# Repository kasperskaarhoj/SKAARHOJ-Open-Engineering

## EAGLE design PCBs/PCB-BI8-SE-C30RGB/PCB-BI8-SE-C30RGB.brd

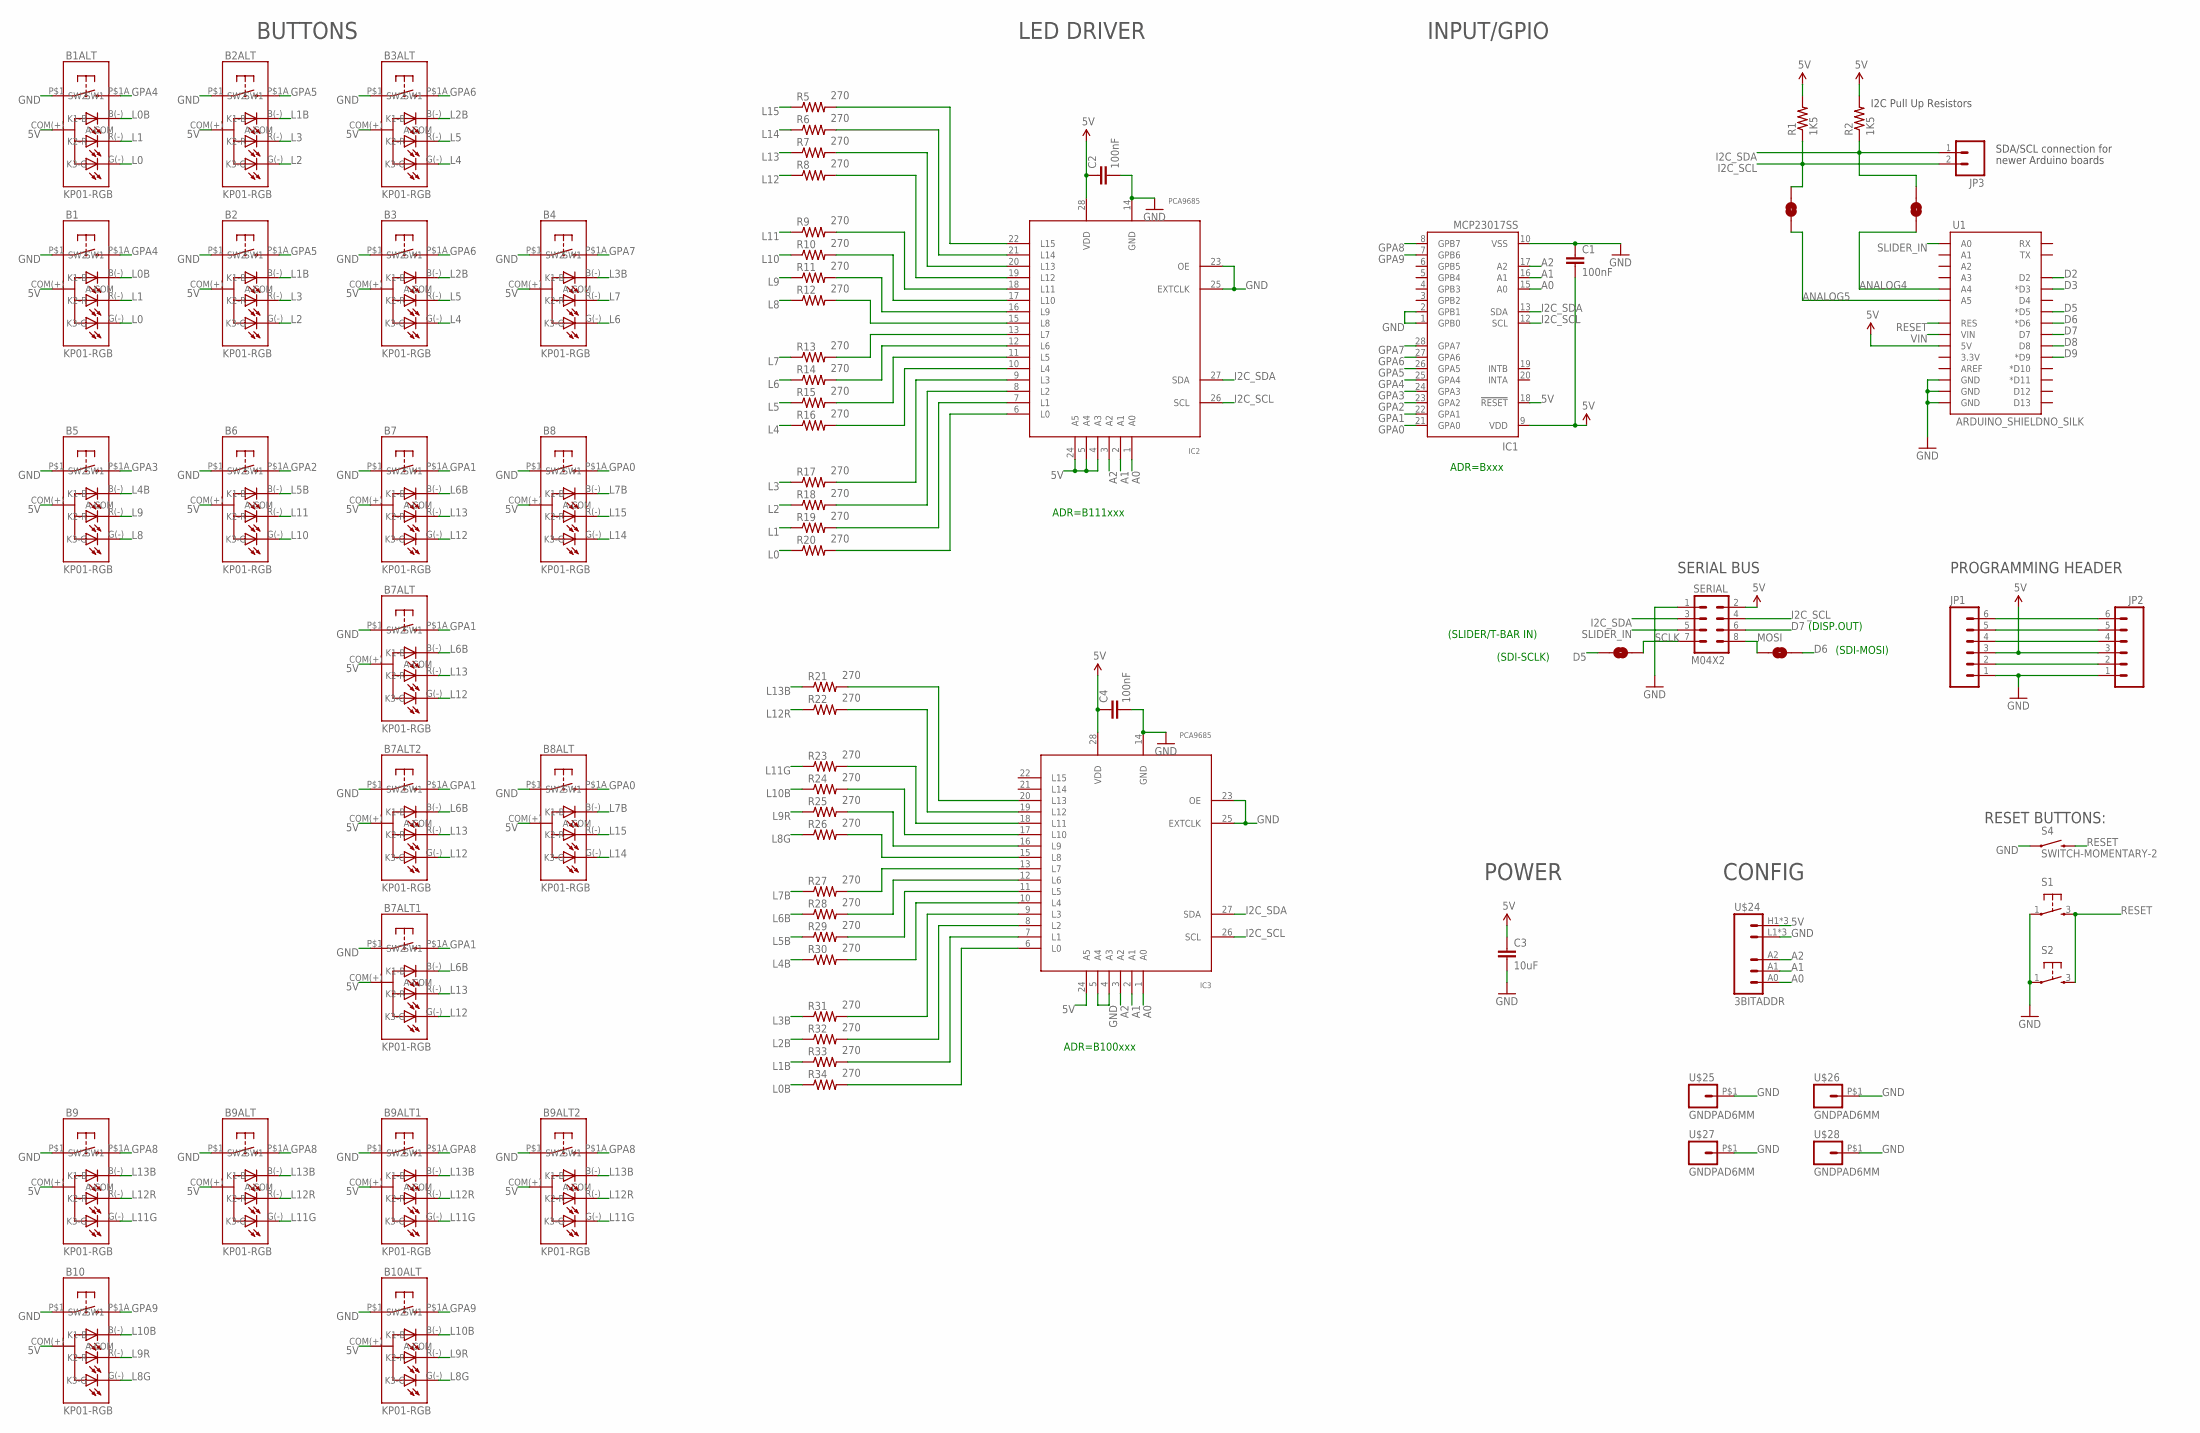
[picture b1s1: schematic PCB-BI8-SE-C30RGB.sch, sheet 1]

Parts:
B1, B1ALT, B2, B2ALT, B3, B3ALT, B4, B5, B7, B8, B9, B10: KP01-RGB; NKK-KP01
B6, B7ALT, B7ALT1, B7ALT2, B8ALT, B9ALT, B9ALT1, B9ALT2, B10ALT: KP01-RGB; NKK-KP01_LESSHOLES
C1, C2, C4: 100nF; 0603-CAP
C3: 10uF; 0805
IC1: MCP23017SS; SSOP28; MPN MCP23017-E/SS
IC2, IC3: PCA9685; TSSOP28
JP1, JP2: M06POLAR; MOLEX-1X6
JP3: M02PTH; 1X02
MOSI->D6: SOLDERJUMPERNC; SJ_2S
R1, R2: 1K5; 0603-RES
R5, R6, R7, R8, R9, R10, R11, R12, R13, R14, R15, R16, R17, R18, R19, R20, R21, R22, R23, R24, R25, R26, R27, R28, R29, R30, R31, R32, R33, R34: 270; 0603-RES
S1, S2: TAC_SWITCH; PUSHBUTTON
S3->A2, S3->A3: SOLDERJUMPERNC; SJ_2S
S4: SWITCH-MOMENTARY-2; TACTILE_SWITCH_TALL
SCLK->D5: SOLDERJUMPERNC; SJ_2S
SERIAL: M04X2; 2X4
U1: ARDUINO_SHIELDNO_SILK; DUEMILANOVE_VIAS
U$24: 3BITADDR
U$25, U$26, U$27, U$28: GNDPAD6MM; 3.2MMPAD6MM

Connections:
5V: B1.COM(+) (A-COM), B1ALT.COM(+) (A-COM), B2.COM(+) (A-COM), B2ALT.COM(+) (A-COM), B3.COM(+) (A-COM), B3ALT.COM(+) (A-COM), B4.COM(+) (A-COM), B5.COM(+) (A-COM), B6.COM(+) (A-COM), B7.COM(+) (A-COM), B7ALT.COM(+) (A-COM), B7ALT1.COM(+) (A-COM), B7ALT2.COM(+) (A-COM), B8.COM(+) (A-COM), B8ALT.COM(+) (A-COM), B9.COM(+) (A-COM), B9ALT.COM(+) (A-COM), B9ALT1.COM(+) (A-COM), B9ALT2.COM(+) (A-COM), B10.COM(+) (A-COM), B10ALT.COM(+) (A-COM), C1.2, C2.1, C3.1, C4.1, IC1.9 (VDD), IC1.18 (!RESET), IC2.4 (A3), IC2.5 (A4), IC2.24 (A5), IC2.28 (VDD), IC3.24 (A5), IC3.28 (VDD), JP1.3, JP2.3, R1.2, R2.2, SERIAL.2, U1.5V, U$24.H1 (VCC), U$24.H2 (VCC), U$24.H3 (VCC)
A0: IC1.15 (A0), IC2.1 (A0), IC3.1 (A0), U$24.A0
A1: IC1.16 (A1), IC2.2 (A1), IC3.2 (A1), U$24.A1
A2: IC1.17 (A2), IC2.3 (A2), IC3.3 (A2), U$24.A2
ANALOG4: S3->A3.2, U1.A4
ANALOG5: S3->A2.2, U1.A5
D2: U1.D2
D3: U1.D3 (*D3)
D5: SCLK->D5.1, U1.D5 (*D5)
D6: MOSI->D6.2, U1.D6 (*D6)
D7: SERIAL.6, U1.D7
D8: U1.D8
D9: U1.D9 (*D9)
GND: B1.P$1 (SW1), B1ALT.P$1 (SW1), B2.P$1 (SW1), B2ALT.P$1 (SW1), B3.P$1 (SW1), B3ALT.P$1 (SW1), B4.P$1 (SW1), B5.P$1 (SW1), B6.P$1 (SW1), B7.P$1 (SW1), B7ALT.P$1 (SW1), B7ALT1.P$1 (SW1), B7ALT2.P$1 (SW1), B8.P$1 (SW1), B8ALT.P$1 (SW1), B9.P$1 (SW1), B9ALT.P$1 (SW1), B9ALT1.P$1 (SW1), B9ALT2.P$1 (SW1), B10.P$1 (SW1), B10ALT.P$1 (SW1), C1.1, C2.2, C3.2, C4.2, IC1.1 (GPB0), IC1.2 (GPB1), IC1.10 (VSS), IC2.14 (GND), IC2.23 (OE), IC2.25 (EXTCLK), IC3.4 (A3), IC3.5 (A4), IC3.14 (GND), IC3.23 (OE), IC3.25 (EXTCLK), JP1.1, JP2.1, S1.1, S2.1, S4.A2 (1), SERIAL.1, U1.GND@0 (GND), U1.GND@1 (GND), U1.GND@2 (GND), U$24.L1 (GND), U$24.L2 (GND), U$24.L3 (GND), U$25.P$1, U$26.P$1, U$27.P$1, U$28.P$1
GPA0: B8.P$1A (SW2), B8ALT.P$1A (SW2), IC1.21 (GPA0)
GPA1: B7.P$1A (SW2), B7ALT.P$1A (SW2), B7ALT1.P$1A (SW2), B7ALT2.P$1A (SW2), IC1.22 (GPA1)
GPA2: B6.P$1A (SW2), IC1.23 (GPA2)
GPA3: B5.P$1A (SW2), IC1.24 (GPA3)
GPA4: B1.P$1A (SW2), B1ALT.P$1A (SW2), IC1.25 (GPA4)
GPA5: B2.P$1A (SW2), B2ALT.P$1A (SW2), IC1.26 (GPA5)
GPA6: B3.P$1A (SW2), B3ALT.P$1A (SW2), IC1.27 (GPA6)
GPA7: B4.P$1A (SW2), IC1.28 (GPA7)
GPA8: B9.P$1A (SW2), B9ALT.P$1A (SW2), B9ALT1.P$1A (SW2), B9ALT2.P$1A (SW2), IC1.8 (GPB7)
GPA9: B10.P$1A (SW2), B10ALT.P$1A (SW2), IC1.7 (GPB6)
I2C_SCL: IC1.12 (SCL), IC2.26 (SCL), IC3.26 (SCL), JP3.2, R1.1, S3->A2.1, SERIAL.4
I2C_SDA: IC1.13 (SDA), IC2.27 (SDA), IC3.27 (SDA), JP3.1, R2.1, S3->A3.1, SERIAL.3
L0: B1.G(-) (K3-G), B1ALT.G(-) (K3-G), R20.1
L0B: B1.B(-) (K1-B), B1ALT.B(-) (K1-B), R34.1
L1: B1.R(-) (K2-R), B1ALT.R(-) (K2-R), R19.1
L1B: B2.B(-) (K1-B), B2ALT.B(-) (K1-B), R33.1
L2: B2.G(-) (K3-G), B2ALT.G(-) (K3-G), R18.1
L2B: B3.B(-) (K1-B), B3ALT.B(-) (K1-B), R32.1
L3: B2.R(-) (K2-R), B2ALT.R(-) (K2-R), R17.1
L3B: B4.B(-) (K1-B), R31.1
L4: B3.G(-) (K3-G), B3ALT.G(-) (K3-G), R16.1
L4B: B5.B(-) (K1-B), R30.1
L5: B3.R(-) (K2-R), B3ALT.R(-) (K2-R), R15.1
L5B: B6.B(-) (K1-B), R29.1
L6: B4.G(-) (K3-G), R14.1
L6B: B7.B(-) (K1-B), B7ALT.B(-) (K1-B), B7ALT1.B(-) (K1-B), B7ALT2.B(-) (K1-B), R28.1
L7: B4.R(-) (K2-R), R13.1
L7B: B8.B(-) (K1-B), B8ALT.B(-) (K1-B), R27.1
L8: B5.G(-) (K3-G), R12.1
L8G: B10.G(-) (K3-G), B10ALT.G(-) (K3-G), R26.1
L9: B5.R(-) (K2-R), R11.1
L9R: B10.R(-) (K2-R), B10ALT.R(-) (K2-R), R25.1
L10: B6.G(-) (K3-G), R10.1
L10B: B10.B(-) (K1-B), B10ALT.B(-) (K1-B), R24.1
L11: B6.R(-) (K2-R), R9.1
L11G: B9.G(-) (K3-G), B9ALT.G(-) (K3-G), B9ALT1.G(-) (K3-G), B9ALT2.G(-) (K3-G), R23.1
L12: B7.G(-) (K3-G), B7ALT.G(-) (K3-G), B7ALT1.G(-) (K3-G), B7ALT2.G(-) (K3-G), R8.1
L12R: B9.R(-) (K2-R), B9ALT.R(-) (K2-R), B9ALT1.R(-) (K2-R), B9ALT2.R(-) (K2-R), R22.1
L13: B7.R(-) (K2-R), B7ALT.R(-) (K2-R), B7ALT1.R(-) (K2-R), B7ALT2.R(-) (K2-R), R7.1
L13B: B9.B(-) (K1-B), B9ALT.B(-) (K1-B), B9ALT1.B(-) (K1-B), B9ALT2.B(-) (K1-B), R21.1
L14: B8.G(-) (K3-G), B8ALT.G(-) (K3-G), R6.1
L15: B8.R(-) (K2-R), B8ALT.R(-) (K2-R), R5.1
MOSI: MOSI->D6.1, SERIAL.8
unnamed: JP1.2, JP2.2
unnamed: IC3.13 (L7), R27.2
unnamed: IC3.12 (L6), R28.2
unnamed: IC2.13 (L7), R13.2
unnamed: IC2.12 (L6), R14.2
unnamed: IC3.11 (L5), R29.2
unnamed: IC2.11 (L5), R15.2
unnamed: IC2.10 (L4), R16.2
unnamed: IC2.9 (L3), R17.2
unnamed: IC2.8 (L2), R18.2
unnamed: IC2.7 (L1), R19.2
unnamed: IC3.10 (L4), R30.2
unnamed: IC3.9 (L3), R31.2
unnamed: IC3.8 (L2), R32.2
unnamed: IC3.7 (L1), R33.2
unnamed: IC3.6 (L0), R34.2
unnamed: IC3.15 (L8), R26.2
unnamed: IC2.6 (L0), R20.2
unnamed: IC2.15 (L8), R12.2
unnamed: IC2.16 (L9), R11.2
unnamed: IC2.17 (L10), R10.2
unnamed: IC2.18 (L11), R9.2
unnamed: IC2.19 (L12), R8.2
unnamed: IC2.20 (L13), R7.2
unnamed: IC2.21 (L14), R6.2
unnamed: IC2.22 (L15), R5.2
unnamed: IC3.16 (L9), R25.2
unnamed: IC3.17 (L10), R24.2
unnamed: IC3.18 (L11), R23.2
unnamed: IC3.19 (L12), R22.2
unnamed: IC3.20 (L13), R21.2
unnamed: JP1.4, JP2.4
unnamed: JP1.5, JP2.5
unnamed: JP1.6, JP2.6
RESET: S1.3, S2.3, S4.B2 (2), U1.RES
SCLK: SCLK->D5.2, SERIAL.7
SLIDER_IN: SERIAL.5, U1.A0
VIN: U1.VIN

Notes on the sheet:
PROGRAMMING HEADER
I2C Pull Up Resistors
SDA/SCL connection for
newer Arduino boards
SERIAL BUS
(SLIDER/T-BAR IN)
(SDI-SCLK)
(SDI-MOSI)
(DISP.OUT)
RESET BUTTONS:
ADR=B111xxx
ADR=Bxxx
BUTTONS
LED DRIVER
INPUT/GPIO
POWER
ADR=B100xxx
CONFIG

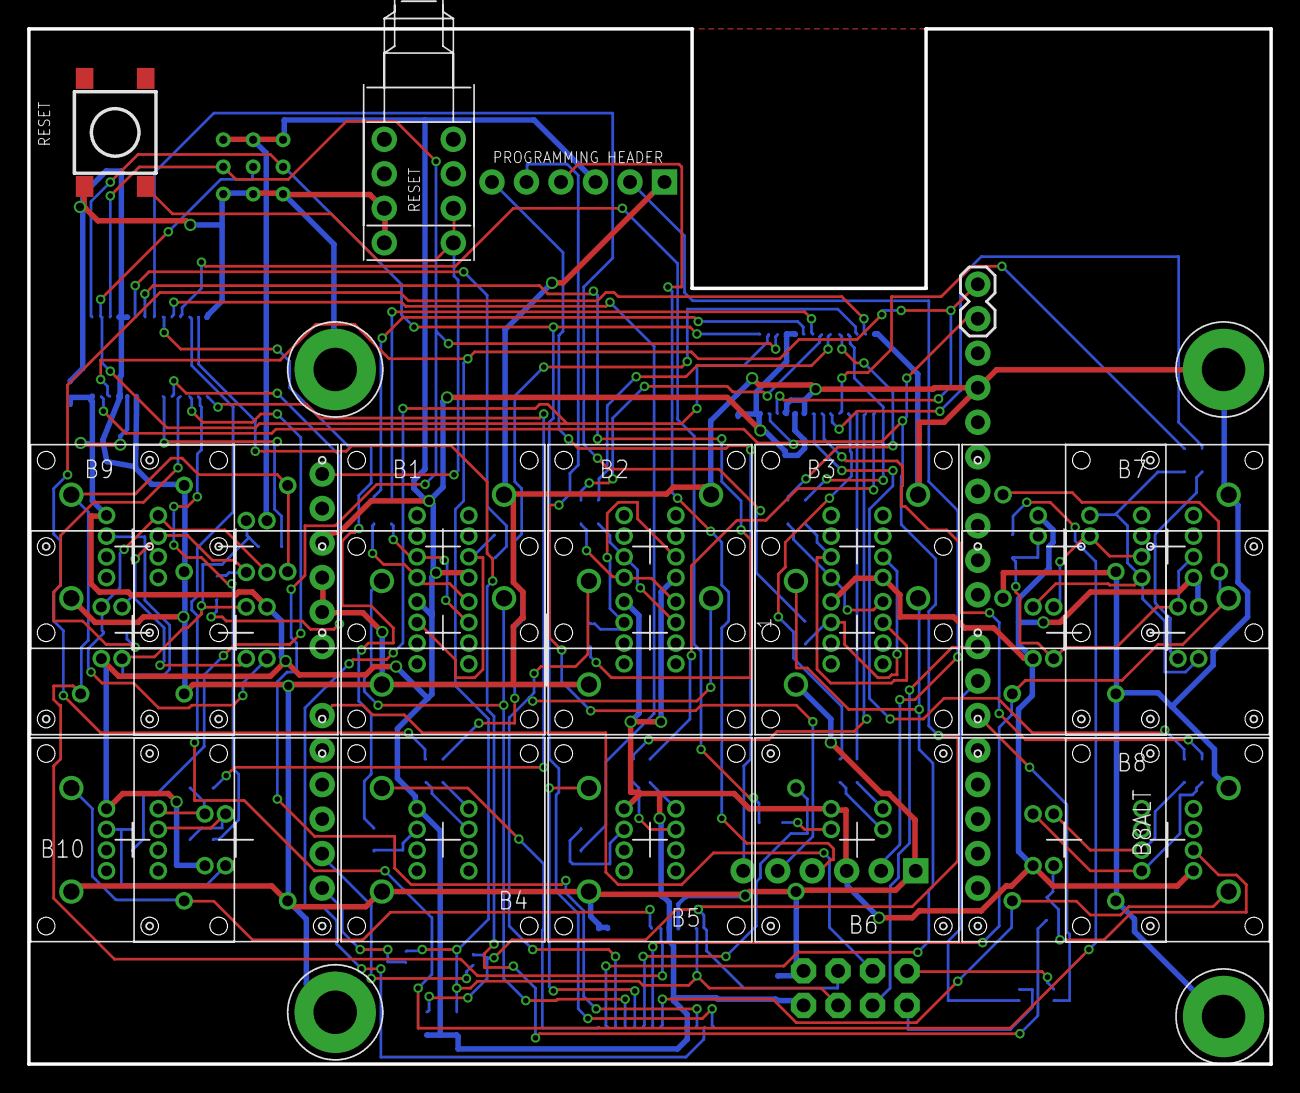
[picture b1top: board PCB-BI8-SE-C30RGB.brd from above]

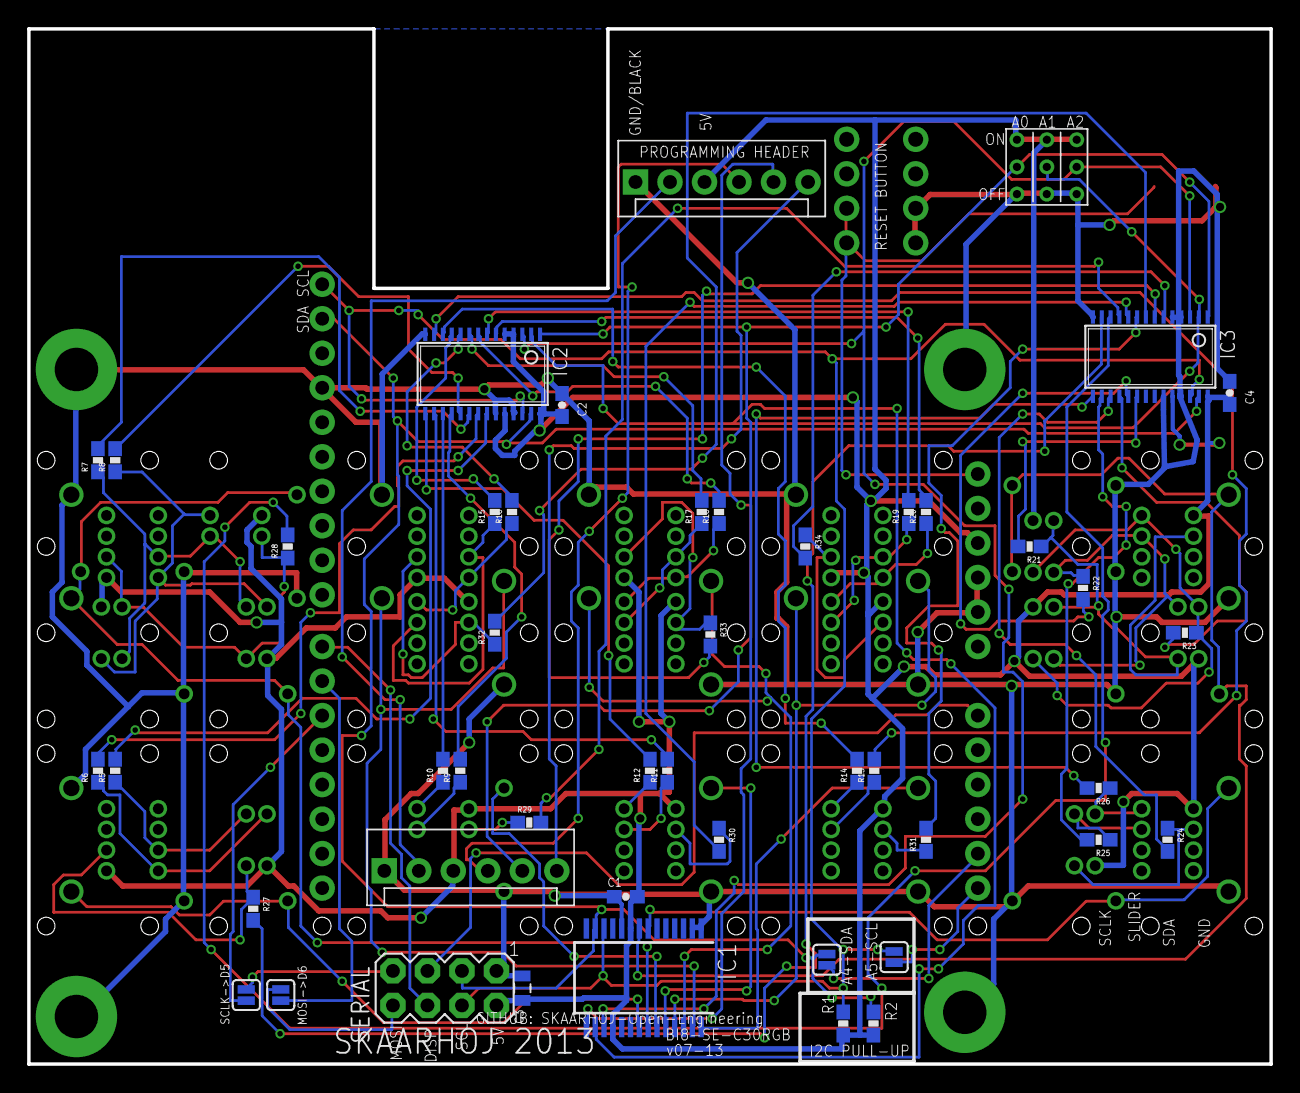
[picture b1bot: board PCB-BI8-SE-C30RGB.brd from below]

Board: 2 copper layers, 91.4 x 76.2 mm, 77 parts (47 on the bottom side), 90 nets.

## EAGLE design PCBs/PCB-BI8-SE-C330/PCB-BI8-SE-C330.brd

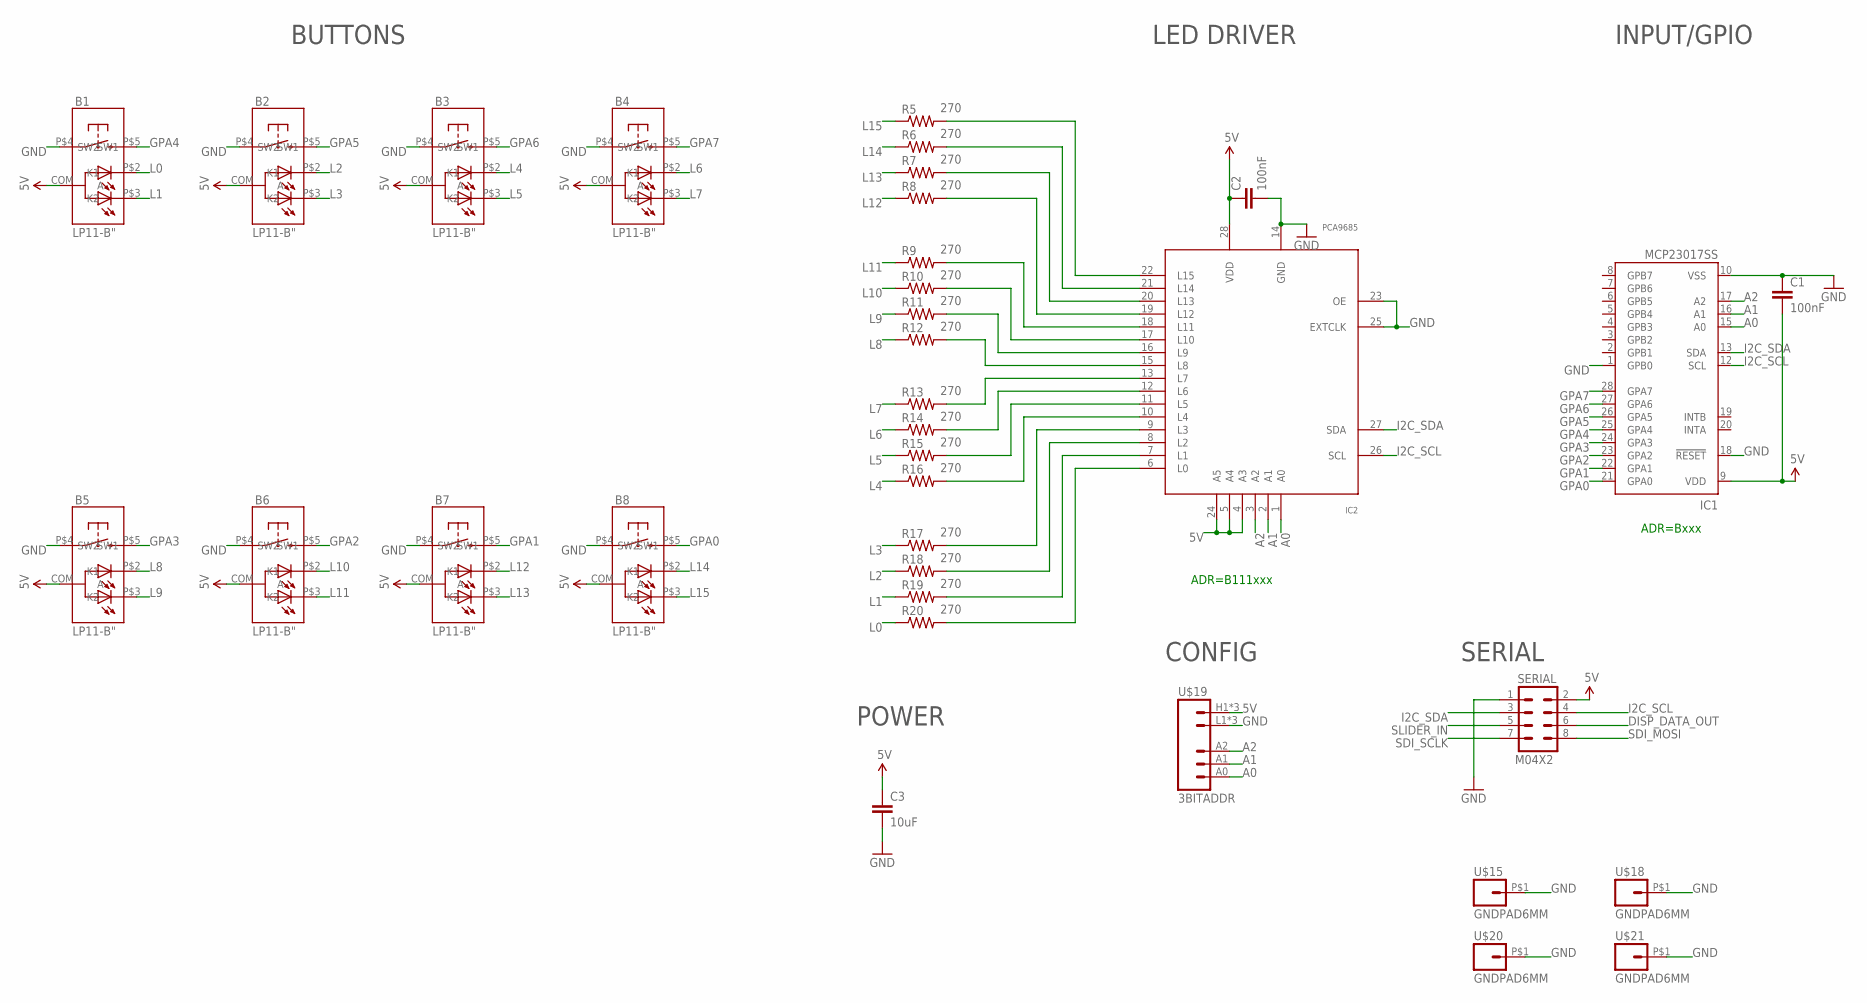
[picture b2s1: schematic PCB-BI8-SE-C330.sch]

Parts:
B1, B2, B3, B4, B5, B6, B7, B8: LP11-B"; LP11
C1, C2: 100nF; 0603-CAP
C3: 10uF; 0805
IC1: MCP23017SS; SSOP28; MPN MCP23017-E/SS
IC2: PCA9685; TSSOP28
R5, R6, R7, R8, R9, R10, R11, R12, R13, R14, R15, R16, R17, R18, R19, R20: 270; 0603-RES
SERIAL: M04X2; 2X4
U$15, U$18, U$20, U$21: GNDPAD6MM; 3.2MMPAD6MM
U$19: 3BITADDR

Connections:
5V: B1.COM (A), B2.COM (A), B3.COM (A), B4.COM (A), B5.COM (A), B6.COM (A), B7.COM (A), B8.COM (A), C1.2, C2.1, C3.1, IC1.9 (VDD), IC2.4 (A3), IC2.5 (A4), IC2.24 (A5), IC2.28 (VDD), SERIAL.2, U$19.H1 (VCC), U$19.H2 (VCC), U$19.H3 (VCC)
A0: IC1.15 (A0), IC2.1 (A0), U$19.A0
A1: IC1.16 (A1), IC2.2 (A1), U$19.A1
A2: IC1.17 (A2), IC2.3 (A2), U$19.A2
DISP_DATA_OUT: SERIAL.6
GND: B1.P$4 (SW1), B2.P$4 (SW1), B3.P$4 (SW1), B4.P$4 (SW1), B5.P$4 (SW1), B6.P$4 (SW1), B7.P$4 (SW1), B8.P$4 (SW1), C1.1, C2.2, C3.2, IC1.1 (GPB0), IC1.10 (VSS), IC1.18 (!RESET), IC2.14 (GND), IC2.23 (OE), IC2.25 (EXTCLK), SERIAL.1, U$15.P$1, U$18.P$1, U$19.L1 (GND), U$19.L2 (GND), U$19.L3 (GND), U$20.P$1, U$21.P$1
GPA0: B8.P$5 (SW2), IC1.21 (GPA0)
GPA1: B7.P$5 (SW2), IC1.22 (GPA1)
GPA2: B6.P$5 (SW2), IC1.23 (GPA2)
GPA3: B5.P$5 (SW2), IC1.24 (GPA3)
GPA4: B1.P$5 (SW2), IC1.25 (GPA4)
GPA5: B2.P$5 (SW2), IC1.26 (GPA5)
GPA6: B3.P$5 (SW2), IC1.27 (GPA6)
GPA7: B4.P$5 (SW2), IC1.28 (GPA7)
I2C_SCL: IC1.12 (SCL), IC2.26 (SCL), SERIAL.4
I2C_SDA: IC1.13 (SDA), IC2.27 (SDA), SERIAL.3
L0: B1.P$2 (K1), R20.1
L1: B1.P$3 (K2), R19.1
L2: B2.P$2 (K1), R18.1
L3: B2.P$3 (K2), R17.1
L4: B3.P$2 (K1), R16.1
L5: B3.P$3 (K2), R15.1
L6: B4.P$2 (K1), R14.1
L7: B4.P$3 (K2), R13.1
L8: B5.P$2 (K1), R12.1
L9: B5.P$3 (K2), R11.1
L10: B6.P$2 (K1), R10.1
L11: B6.P$3 (K2), R9.1
L12: B7.P$2 (K1), R8.1
L13: B7.P$3 (K2), R7.1
L14: B8.P$2 (K1), R6.1
L15: B8.P$3 (K2), R5.1
unnamed: IC2.13 (L7), R13.2
unnamed: IC2.12 (L6), R14.2
unnamed: IC2.11 (L5), R15.2
unnamed: IC2.10 (L4), R16.2
unnamed: IC2.9 (L3), R17.2
unnamed: IC2.8 (L2), R18.2
unnamed: IC2.7 (L1), R19.2
unnamed: IC2.6 (L0), R20.2
unnamed: IC2.15 (L8), R12.2
unnamed: IC2.16 (L9), R11.2
unnamed: IC2.17 (L10), R10.2
unnamed: IC2.18 (L11), R9.2
unnamed: IC2.19 (L12), R8.2
unnamed: IC2.20 (L13), R7.2
unnamed: IC2.21 (L14), R6.2
unnamed: IC2.22 (L15), R5.2
SDI_MOSI: SERIAL.8
SDI_SCLK: SERIAL.7
SLIDER_IN: SERIAL.5

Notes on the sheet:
ADR=B111xxx
ADR=Bxxx
BUTTONS
LED DRIVER
INPUT/GPIO
POWER
SERIAL
CONFIG

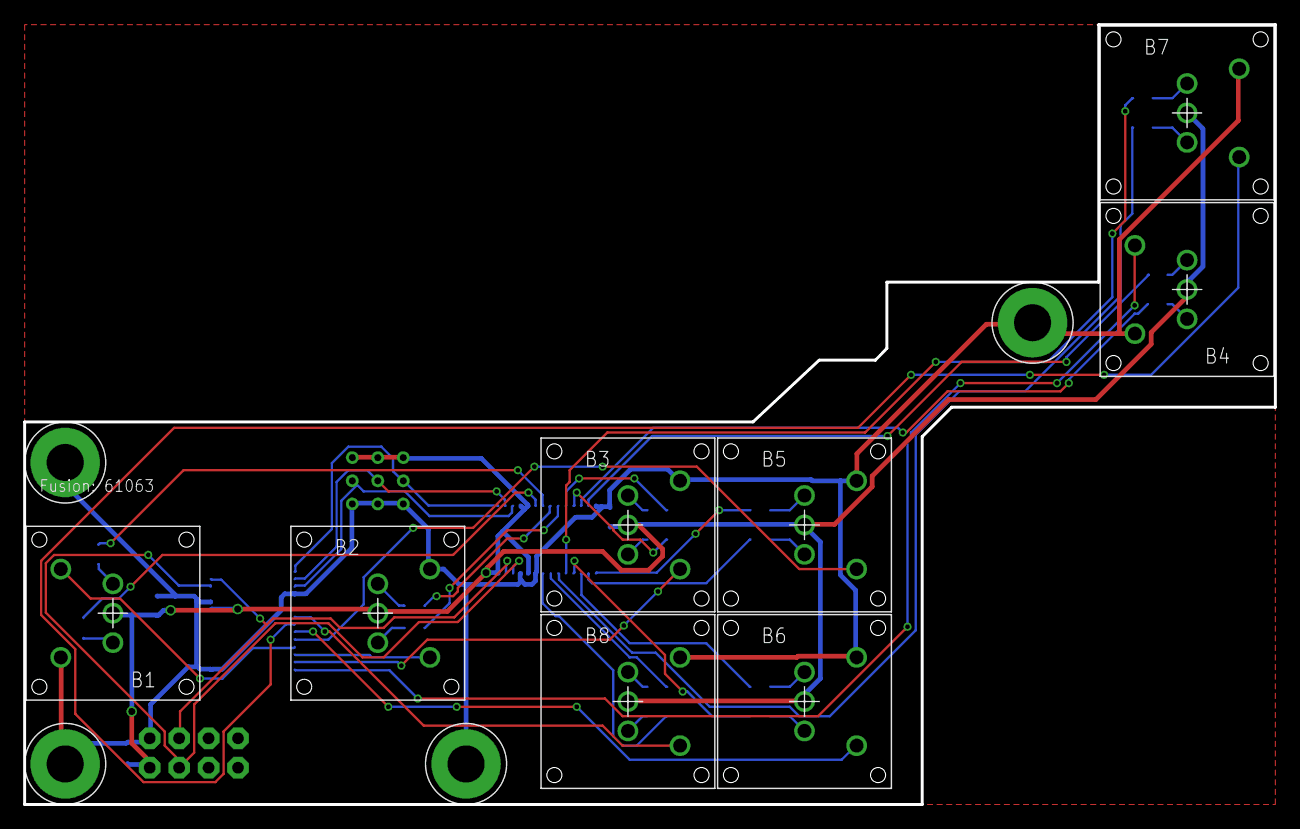
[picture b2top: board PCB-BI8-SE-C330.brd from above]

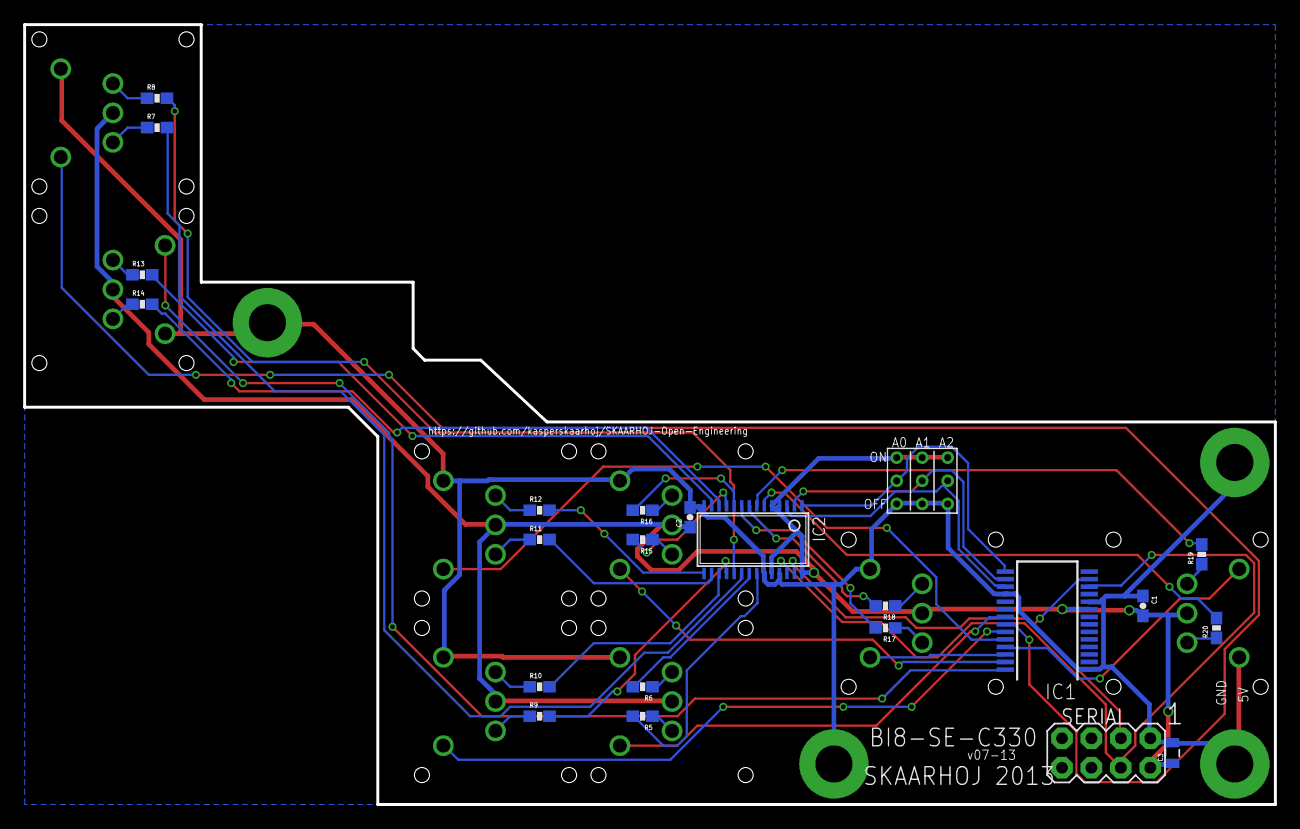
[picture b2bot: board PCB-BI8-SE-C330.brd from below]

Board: 2 copper layers, 108.0 x 67.3 mm, 35 parts (23 on the bottom side), 47 nets.

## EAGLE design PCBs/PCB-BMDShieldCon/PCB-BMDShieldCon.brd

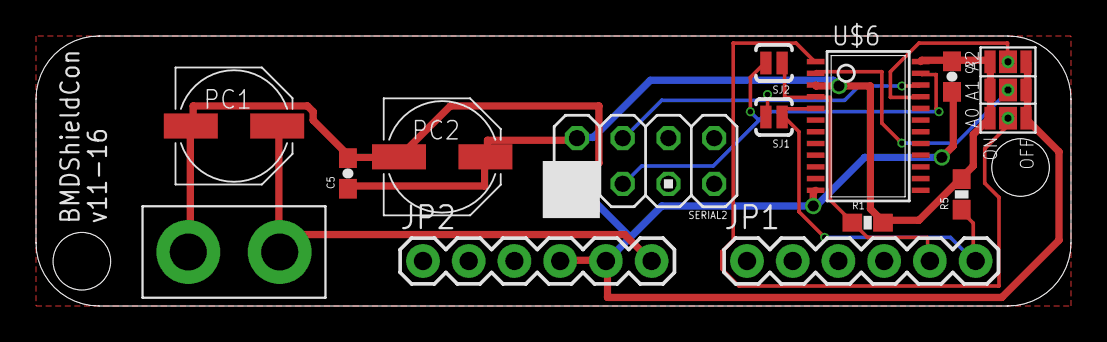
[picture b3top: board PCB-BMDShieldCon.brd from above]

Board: 4 copper layers, 57.5 x 15.0 mm, 14 parts (0 on the bottom side), 10 nets.

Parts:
C2, C5: 100nF; 0603-CAP
JP1, JP2: 1X06
JP3: 1X02_XTRA_BIG
PC1, PC2: 47u; PANASONIC_D
R1, R5: 1K8; 0603-RES
SERIAL2: M04X2M2X4SMALLER; M2X4SMALLER
SJ1, SJ2: SOLDERJUMPERNO; SJ_2S-NO
U$2: 3BITADDRSMALL; 3BITADDR_SMALL
U$6: TCA9548A; TSSOP24

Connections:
5V: C2.1, C5.1, PC2.+, R1.2, R5.2, SERIAL2.2, U$2.H0, U$2.H1, U$2.H2, U$6.3, U$6.24
GND: C2.2, C5.2, JP2.4, JP2.5, JP3.1, PC1.-, PC2.-, SERIAL2.1, U$2.L0, U$2.L1, U$2.L2, U$6.12
I2C_SCL: SERIAL2.4, SJ1.2, U$6.22
I2C_SDA: SERIAL2.3, SJ2.2, U$6.23
unnamed: JP1.6, R5.1, SJ1.1, U$6.5
unnamed: JP2.6, JP3.2, PC1.+
unnamed: JP1.5, R1.1, SJ2.1, U$6.4
unnamed: U$2.A0, U$2.AS0, U$6.1
unnamed: U$2.A1, U$2.AS1, U$6.2
unnamed: U$2.A2, U$2.AS2, U$6.21

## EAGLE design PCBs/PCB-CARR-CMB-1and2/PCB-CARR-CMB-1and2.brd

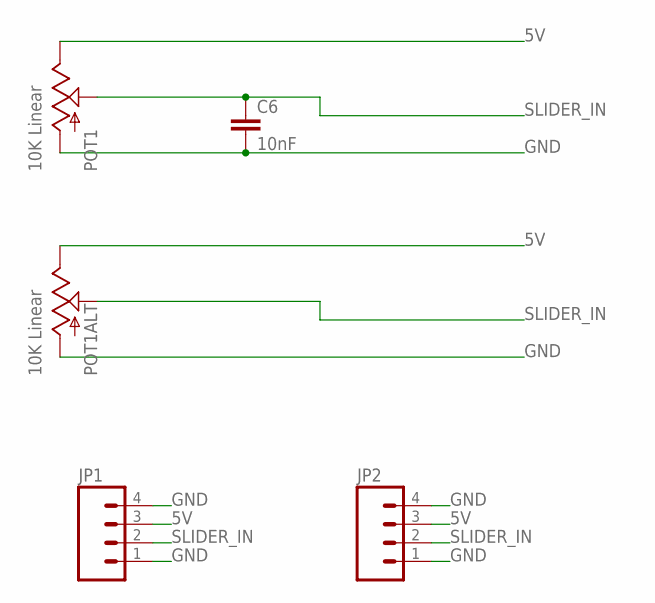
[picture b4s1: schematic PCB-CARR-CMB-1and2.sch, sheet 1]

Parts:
C6: 10nF; 0603-CAP
JP1, JP2: M04PTH; 1X04
POT1, POT1ALT: 10K Linear; SLIDER20

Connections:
5V: JP1.3, JP2.3, POT1.1 (E), POT1ALT.1 (E)
GND: C6.2, JP1.1, JP1.4, JP2.1, JP2.4, POT1.3 (A), POT1ALT.3 (A)
SLIDER_IN: C6.1, JP1.2, JP2.2, POT1.2A (S), POT1ALT.2A (S)

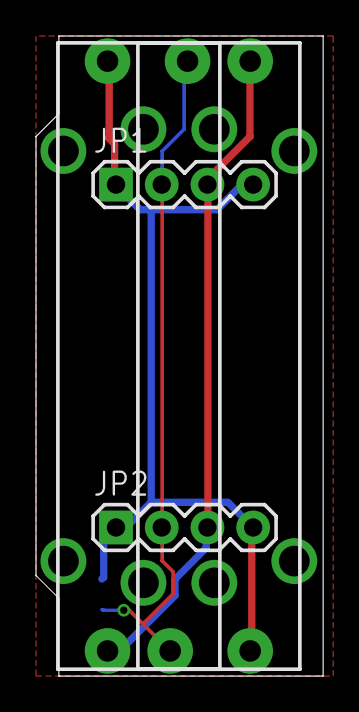
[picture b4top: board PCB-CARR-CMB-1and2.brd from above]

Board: 2 copper layers, 16.0 x 35.6 mm, 5 parts (1 on the bottom side), 3 nets.

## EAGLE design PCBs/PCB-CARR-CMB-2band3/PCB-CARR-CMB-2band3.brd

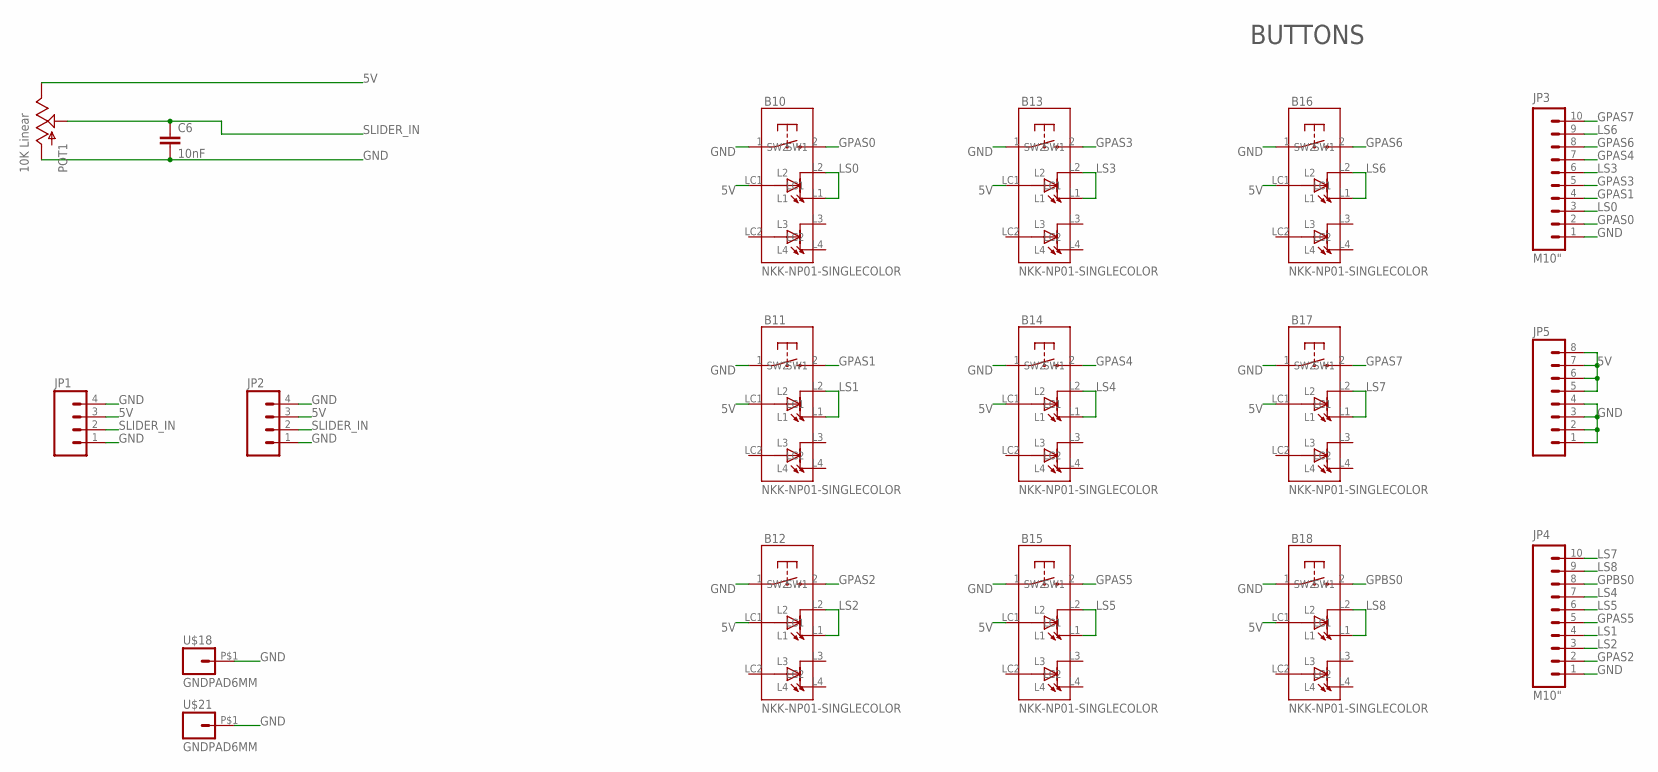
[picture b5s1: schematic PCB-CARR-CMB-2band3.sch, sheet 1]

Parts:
B10, B11, B12, B13, B14, B15, B16, B17, B18: NKK-NP01-SINGLECOLOR; NKK-NP01
C6: 10nF; 0603-CAP
JP1, JP2: M04PTH; 1X04
JP3, JP4: M10"; 1X10
JP5: M08LOCK; 1X08_LOCK
POT1: 10K Linear; SLIDER20
U$18, U$21: GNDPAD6MM; 3.2MMPAD6MM

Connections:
5V: B10.LC1, B11.LC1, B12.LC1, B13.LC1, B14.LC1, B15.LC1, B16.LC1, B17.LC1, B18.LC1, JP1.3, JP2.3, JP5.5, JP5.6, JP5.7, JP5.8, POT1.1 (E)
GND: B10.1 (SW1), B11.1 (SW1), B12.1 (SW1), B13.1 (SW1), B14.1 (SW1), B15.1 (SW1), B16.1 (SW1), B17.1 (SW1), B18.1 (SW1), C6.2, JP1.1, JP1.4, JP2.1, JP2.4, JP3.1, JP4.1, JP5.1, JP5.2, JP5.3, JP5.4, POT1.3 (A), U$18.P$1, U$21.P$1
GPAS0: B10.2 (SW2), JP3.2
GPAS1: B11.2 (SW2), JP3.4
GPAS2: B12.2 (SW2), JP4.2
GPAS3: B13.2 (SW2), JP3.5
GPAS4: B14.2 (SW2), JP3.7
GPAS5: B15.2 (SW2), JP4.5
GPAS6: B16.2 (SW2), JP3.8
GPAS7: B17.2 (SW2), JP3.10
GPBS0: B18.2 (SW2), JP4.8
LS0: B10.L1, B10.L2, JP3.3
LS1: B11.L1, B11.L2, JP4.4
LS2: B12.L1, B12.L2, JP4.3
LS3: B13.L1, B13.L2, JP3.6
LS4: B14.L1, B14.L2, JP4.7
LS5: B15.L1, B15.L2, JP4.6
LS6: B16.L1, B16.L2, JP3.9
LS7: B17.L1, B17.L2, JP4.10
LS8: B18.L1, B18.L2, JP4.9
SLIDER_IN: C6.1, JP1.2, JP2.2, POT1.2A (S)

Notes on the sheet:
BUTTONS

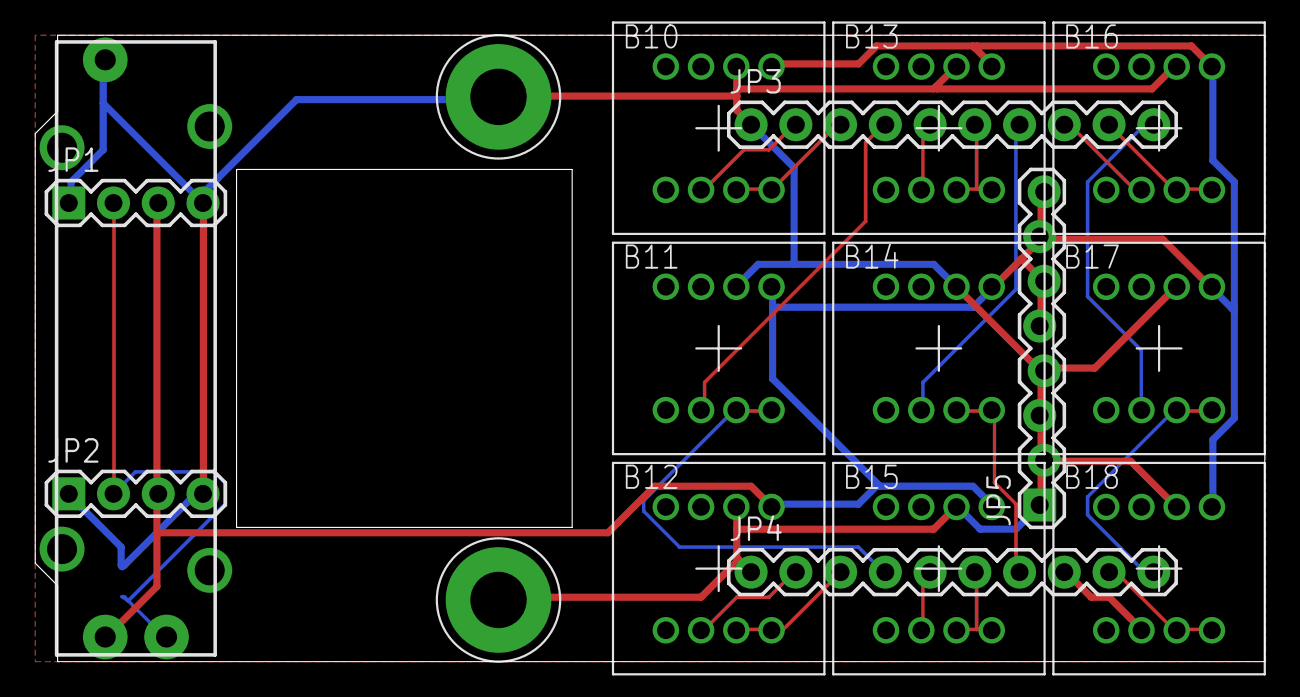
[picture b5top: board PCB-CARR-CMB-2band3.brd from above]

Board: 2 copper layers, 69.8 x 35.6 mm, 18 parts (1 on the bottom side), 21 nets.

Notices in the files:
parts and their libraries:
SparkFun: Licensing: CC v3.0 Share-Alike You are welcome to use this library for commercial purposes.
